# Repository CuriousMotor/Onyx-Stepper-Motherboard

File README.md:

# Onyx-Stepper-Motherboard

The Arduino UNO + CNC shield has been the go-to setup for several CNC machines, robotic arms, drawing machines and what not! It's about time we replace the 8-bit microcontroller, with a powerful 32-bit, Wifi + BLE enabled ESP32!

**Bonus: It's 100% open source, including the PCB layout files!**

This project builds upon pioneering work done by GitHub user [Barton Dring](https://github.com/bdring).

## 3D Model
A 3D model of the PCB can be conveniently viewed in the browser via **CADFlux**.
 - [Basic Model](https://www.cadflux.com/viewer?modelFile=experimental/users/siddharth_kothari/Onyx_PCB_Light.step) (loads faster)
 - [Detailed Model](https://www.cadflux.com/viewer?modelFile=experimental/users/siddharth_kothari/Onyx_PCB.step)

## Blog
[Here's a short blog on how this board was designed!](https://curiousmotor.com/2021/12/27/designing-the-onyx-v1-0-motherboard/)

## Features

1. Control upto 4 stepper motors
2. Supports all stepper drivers in STEP/DIR mode (A4988, DRV8825, TMC2208, TMC2209, TMC2130)
3. 5V PWM outputs x 3
4. Limit switch ports x 3 (X, Y and Z Axes)
5. 12/24V input power supply port
6. Wifi + BLE support (Thanks to GRBL_ESP32)
7. MicroSD card Support

## Firmware

Currently the firmware works superb with GRBL_ESP32. We are in the process of adding support for Marlin.

## Hardware

All of the hardware is designed in **KiCAD**. It's a 2 layer PCB the uses all standard components available at JLCPCB. Currently the board only supports stepper drives in STEP/DIR mode, v2 would support SPI and UART as well.

## Contributors

## Current Progress
Onyx V1 has been thoroughly tested with a 'Dremel CNC', and it works like a charm. We are already ideating and working on a much more powerful V2!

## Support and Sponsorship
We believe open source is the future, collaboration over competition. A lot of time and money goes into development and prototyping. If such projects make your work easier, consider '⭐-ing' the repository. (Yes, that's all it takes!)

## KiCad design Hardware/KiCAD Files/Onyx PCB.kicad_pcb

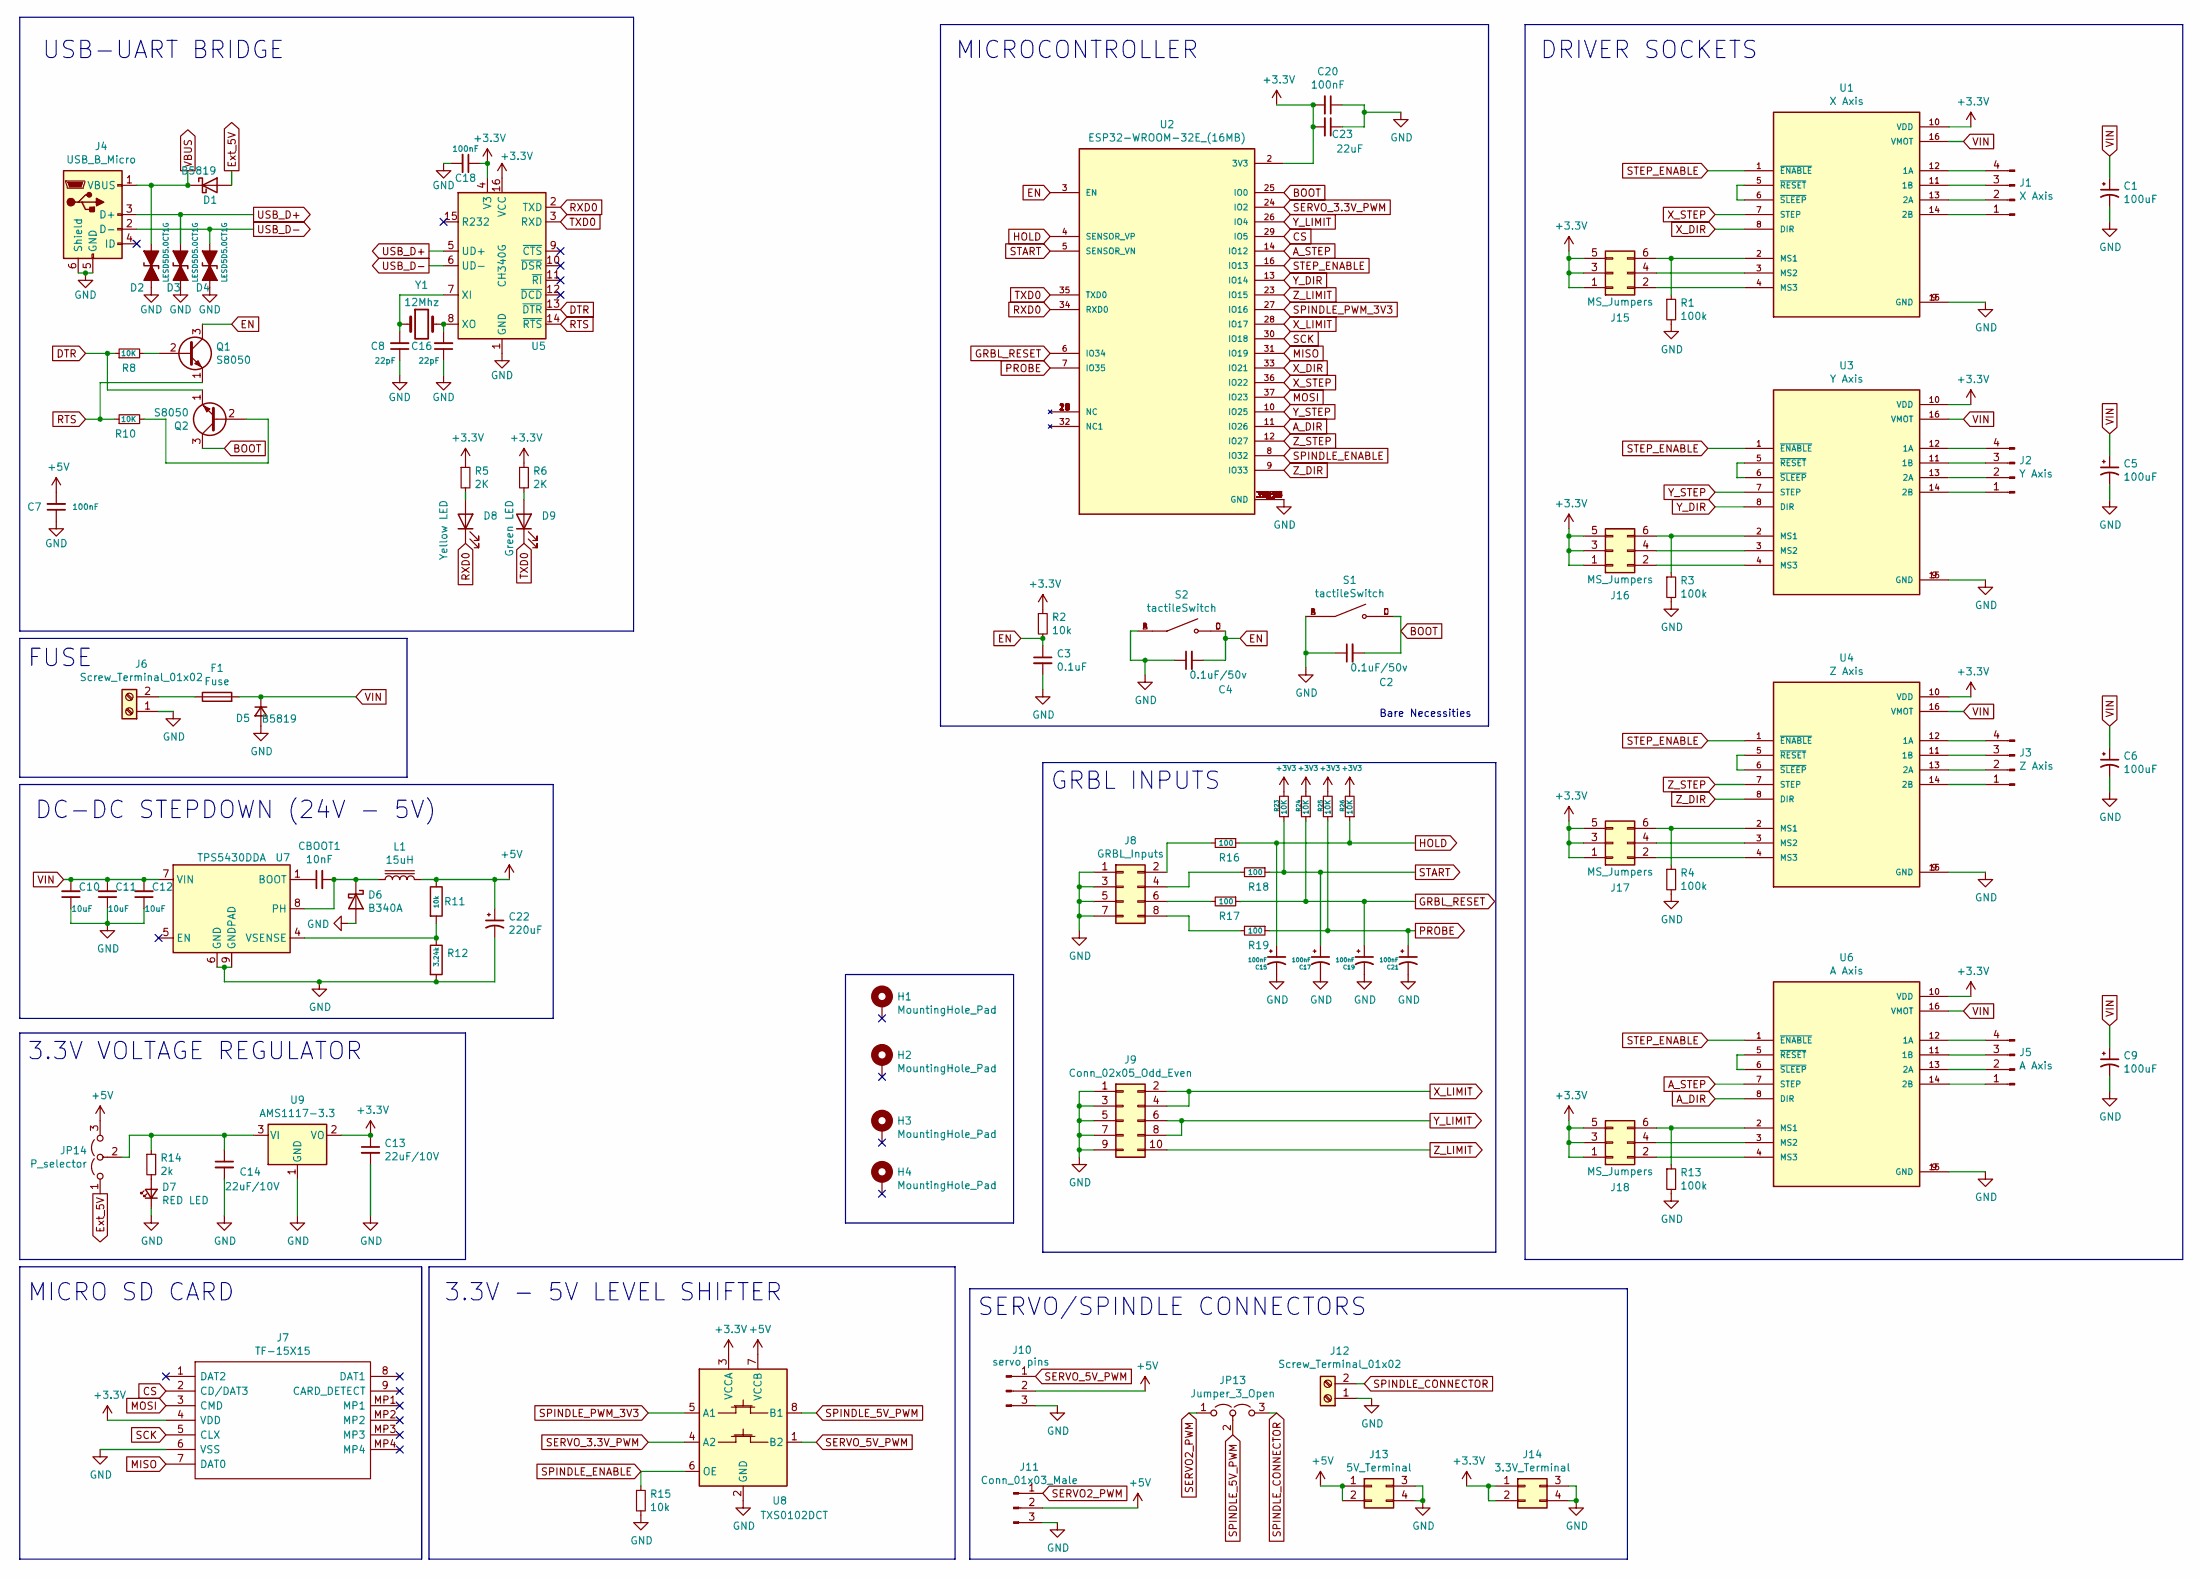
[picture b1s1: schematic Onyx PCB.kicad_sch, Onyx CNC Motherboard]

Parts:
C1, C5, C6, C9: 100uF; CP_Elec_6.3x7.7
C2, C4: 0.1uF/50v; C_0603_1608Metric
C3: 0.1uF; C_0603_1608Metric
C7, C18, C20: 100nF; C_0603_1608Metric
C8, C16: 22pF; C_0603_1608Metric
C10, C11, C12: 10uF; C_0805_2012Metric
C13, C14: 22uF/10V; C_1206_3216Metric
C15, C17, C19, C21: 100nF; C_0402_1005Metric
C22: 220uF; CP_Elec_8x10
C23: 22uF; C_0603_1608Metric; JLCPCB C59461
CBOOT1: 10nF; C_0603_1608Metric
D1, D5: B5819; D_SOD-123
D2, D3, D4: LESD5D5.0CT1G; D_SOD-523
D6: B340A; D_SMA
D7: RED LED; LED_0603_1608Metric
D8: Yellow LED; LED_0603_1608Metric
D9: Green LED; LED_0603_1608Metric
F1: Fuse; R_Axial_DIN0414_L11.9mm_D4.5mm_P20.32mm_Horizontal
H1, H2, H3, H4: MountingHole_Pad; MountingHole_3.2mm_M3_DIN965_Pad
J1: X Axis; PinHeader_1x04_P2.54mm_Vertical
J2: Y Axis; PinHeader_1x04_P2.54mm_Vertical
J3: Z Axis; PinHeader_1x04_P2.54mm_Vertical
J4: USB_B_Micro; USB_Micro-B_Amphenol_10118194_Horizontal; JLCPCB C132563
J5: A Axis; PinHeader_1x04_P2.54mm_Vertical
J6, J12: Screw_Terminal_01x02; TerminalBlock_bornier-2_P5.08mm
J7: TF-15X15; TF15X15; Manufacturer_Part_Number TF-15X15
J8: GRBL_Inputs; PinHeader_2x04_P2.54mm_Vertical
J9: Conn_02x05_Odd_Even; PinHeader_2x05_P2.54mm_Vertical
J10: servo pins; PinHeader_1x03_P2.54mm_Vertical
J11: Conn_01x03_Male; PinHeader_1x03_P2.54mm_Vertical
J13: 5V_Terminal; PinHeader_2x02_P2.54mm_Vertical
J14: 3.3V_Terminal; PinHeader_2x02_P2.54mm_Vertical
J15, J16, J17, J18: MS_Jumpers; PinHeader_2x03_P2.54mm_Vertical
JP13: Jumper_3_Open; PinHeader_1x03_P2.54mm_Vertical
JP14: P_selector; PinHeader_1x03_P2.54mm_Vertical
L1: 15uH; SWRH1207B; JLCPCB C115137
Q1, Q2: S8050; SOT-23
R1: 100k; R_0603_1608Metric; JLCPCB C25803
R2, R11: 10k; R_0805_2012Metric
R3, R4, R13: 100k; R_0603_1608Metric
R5, R6: 2K; R_0805_2012Metric
R8, R10: 10K; R_0805_2012Metric
R12: 3.24k; R_0805_2012Metric
R14: 2k; R_0805_2012Metric
R15: 10k; R_0603_1608Metric
R16, R17, R18, R19: 100; R_0805_2012Metric
R23, R24, R25, R26: 10K; R_0603_1608Metric
S1, S2: tactileSwitch; SW_TS-1187A-B-A-B; PARTREV A0
U1: X Axis; MODULE_A4988_STEPPER_MOTOR_DRIVER_CARRIER
U2: ESP32-WROOM-32E_(16MB); MODULE_ESP32-WROOM-32E_(16MB); PARTREV 1.1
U3: Y Axis; MODULE_A4988_STEPPER_MOTOR_DRIVER_CARRIER
U4: Z Axis; MODULE_A4988_STEPPER_MOTOR_DRIVER_CARRIER
U5: CH340G; SOIC-16_3.9x9.9mm_P1.27mm
U6: A Axis; MODULE_A4988_STEPPER_MOTOR_DRIVER_CARRIER
U7: TPS5430DDA; TI_SO-PowerPAD-8_ThermalVias
U8: TXS0102DCT; SSOP-8_2.95x2.8mm_P0.65mm
U9: AMS1117-3.3; SOT-223-3_TabPin2
Y1: 12Mhz; Crystal_SMD_HC49-SD; JLCPCB C188206

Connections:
+5V: C7.2, C22.1, J10.2, J11.2, J13.1, J13.2, JP14.3 (B), L1.2, R11.1, U8.7 (VCCB)
A_DIR: U2.11 (IO26), U6.8 (DIR)
A_STEP: U2.14 (IO12), U6.7 (STEP)
BOOT: C2.2, Q2.3 (C), S1.C, S1.D, U2.25 (IO0)
CS: J7.2 (CD/DAT3), U2.29 (IO5)
DTR: Q2.1 (E), R8.1, U5.13 (~DTR)
EN: C3.1, C4.2, Q1.3 (C), R2.2, S2.C, S2.D, U2.3 (EN)
Ext_5V: D1.2 (A), JP14.1 (A)
GND: C1.2, C2.1, C3.2, C4.1, C5.2, C6.2, C7.1, C8.1, C9.2, C10.1, C11.1, C12.1, C13.2, C14.2, C15.2, C16.1, C17.2, C18.2, C19.2, C20.1, C21.2, C22.2, C23.1, D2.2 (A2), D3.2 (A2), D4.2 (A2), D5.2 (A), D6.2 (A), D7.1 (K), J4.5 (GND), J4.6 (Shield), J6.1, J7.6 (VSS), J8.1, J8.3, J8.5, J8.7, J9.1, J9.3, J9.5, J9.7, J9.9, J10.3, J11.3, J12.1, J13.3, J13.4, J14.3, J14.4, R1.2, R3.2, R4.2, R12.2, R13.2, R15.2, S1.A, S1.B, S2.A, S2.B, U1.9 (GND), U1.15 (GND), U2.1 (GND), U2.15 (GND), U2.38 (GND), U2.39_1 (GND), U2.39_2 (GND), U2.39_3 (GND), U2.39_4 (GND), U2.39_5 (GND), U2.39_6 (GND), U2.39_7 (GND), U2.39_8 (GND), U2.39_9 (GND), U2.39_10 (GND), U2.39_11 (GND), U2.39_12 (GND), U2.39_13 (GND), U2.39_14 (GND), U2.39_15 (GND), U2.39_16 (GND), U2.39_17 (GND), U2.39_18 (GND), U2.39_19 (GND), U2.39_20 (GND), U2.39_21 (GND), U3.9 (GND), U3.15 (GND), U4.9 (GND), U4.15 (GND), U5.1 (GND), U6.9 (GND), U6.15 (GND), U7.6 (GND), U7.9 (GNDPAD), U8.2 (GND), U9.1 (GND)
GRBL_RESET: C19.1, R17.1, R24.1, U2.6 (IO34)
HOLD: C15.1, R16.1, R26.1, U2.4 (SENSOR_VP)
MISO: J7.7 (DAT0), U2.31 (IO19)
MOSI: J7.3 (CMD), U2.37 (IO23)
unnamed: C8.2, U5.7 (XI), Y1.1
unnamed: C14.1, JP14.2 (C), R14.1, U9.3 (VI)
unnamed: C16.2, U5.8 (XO), Y1.2
unnamed: CBOOT1.1, U7.1 (BOOT)
unnamed: CBOOT1.2, D6.1 (K), L1.1, U7.8 (PH)
unnamed: D7.2 (A), R14.2
unnamed: D8.2 (A), R5.2
unnamed: D9.2 (A), R6.2
unnamed: F1.1, J6.2
unnamed: J1.1, U1.14 (2B)
unnamed: J1.2, U1.13 (2A)
unnamed: J1.3, U1.11 (1B)
unnamed: J1.4, U1.12 (1A)
unnamed: J2.1, U3.14 (2B)
unnamed: J2.2, U3.13 (2A)
unnamed: J2.3, U3.11 (1B)
unnamed: J2.4, U3.12 (1A)
unnamed: J3.1, U4.14 (2B)
unnamed: J3.2, U4.13 (2A)
unnamed: J3.3, U4.11 (1B)
unnamed: J3.4, U4.12 (1A)
unnamed: J5.1, U6.14 (2B)
unnamed: J5.2, U6.13 (2A)
unnamed: J5.3, U6.11 (1B)
unnamed: J5.4, U6.12 (1A)
unnamed: J8.2, R16.2
unnamed: J8.4, R18.2
unnamed: J8.6, R17.2
unnamed: J8.8, R19.2
unnamed: J15.2, U1.4 (MS3)
unnamed: J15.4, U1.3 (MS2)
unnamed: J15.6, R1.1, U1.2 (MS1)
unnamed: J16.2, U3.4 (MS3)
unnamed: J16.4, U3.3 (MS2)
unnamed: J16.6, R3.1, U3.2 (MS1)
unnamed: J17.2, U4.4 (MS3)
unnamed: J17.4, U4.3 (MS2)
unnamed: J17.6, R4.1, U4.2 (MS1)
unnamed: J18.2, U6.4 (MS3)
unnamed: J18.4, U6.3 (MS2)
unnamed: J18.6, R13.1, U6.2 (MS1)
unnamed: Q1.2 (B), R8.2
unnamed: Q2.2 (B), R10.2
unnamed: R11.2, R12.1, U7.4 (VSENSE)
unnamed: U1.5 (~RESET), U1.6 (~SLEEP)
unnamed: U3.5 (~RESET), U3.6 (~SLEEP)
unnamed: U4.5 (~RESET), U4.6 (~SLEEP)
unnamed: U6.5 (~RESET), U6.6 (~SLEEP)
PROBE: C21.1, R19.1, R25.1, U2.7 (IO35)
RTS: Q1.1 (E), R10.1, U5.14 (~RTS)
RXD0: D8.1 (K), U2.34 (RXD0), U5.2 (TXD)
SCK: J7.5 (CLX), U2.30 (IO18)
SERVO2_PWM: J11.1, JP13.1 (A)
SERVO_3.3V_PWM: U2.24 (IO2), U8.4 (A2)
SERVO_5V_PWM: J10.1, U8.1 (B2)
SPINDLE_5V_PWM: JP13.2 (C), U8.8 (B1)
SPINDLE_CONNECTOR: J12.2, JP13.3 (B)
SPINDLE_ENABLE: R15.1, U2.8 (IO32), U8.6 (OE)
SPINDLE_PWM_3V3: U2.27 (IO16), U8.5 (A1)
START: C17.1, R18.1, R23.1, U2.5 (SENSOR_VN)
STEP_ENABLE: U1.1 (~ENABLE), U2.16 (IO13), U3.1 (~ENABLE), U4.1 (~ENABLE), U6.1 (~ENABLE)
TXD0: D9.1 (K), U2.35 (TXD0), U5.3 (RXD)
USB_D+: D3.1 (A1), J4.3 (D+), U5.5 (UD+)
USB_D-: D4.1 (A1), J4.2 (D-), U5.6 (UD-)
VBUS: D1.1 (K), D2.1 (A1), J4.1 (VBUS)
VIN: C1.1, C5.1, C6.1, C9.1, C10.2, C11.2, C12.2, D5.1 (K), F1.2, U1.16 (VMOT), U3.16 (VMOT), U4.16 (VMOT), U6.16 (VMOT), U7.7 (VIN)
X_DIR: U1.8 (DIR), U2.33 (IO21)
X_LIMIT: J9.2, J9.4, U2.28 (IO17)
X_STEP: U1.7 (STEP), U2.36 (IO22)
Y_DIR: U2.13 (IO14), U3.8 (DIR)
Y_LIMIT: J9.6, J9.8, U2.26 (IO4)
Y_STEP: U2.10 (IO25), U3.7 (STEP)
Z_DIR: U2.9 (IO33), U4.8 (DIR)
Z_LIMIT: J9.10, U2.23 (IO15)
Z_STEP: U2.12 (IO27), U4.7 (STEP)

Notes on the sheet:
DRIVER SOCKETS
Bare Necessities
3.3V VOLTAGE REGULATOR
FUSE
SERVO/SPINDLE CONNECTORS
3.3V - 5V LEVEL SHIFTER
MICRO SD CARD
MICROCONTROLLER
DC-DC STEPDOWN (24V - 5V)
USB-UART BRIDGE
GRBL INPUTS

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
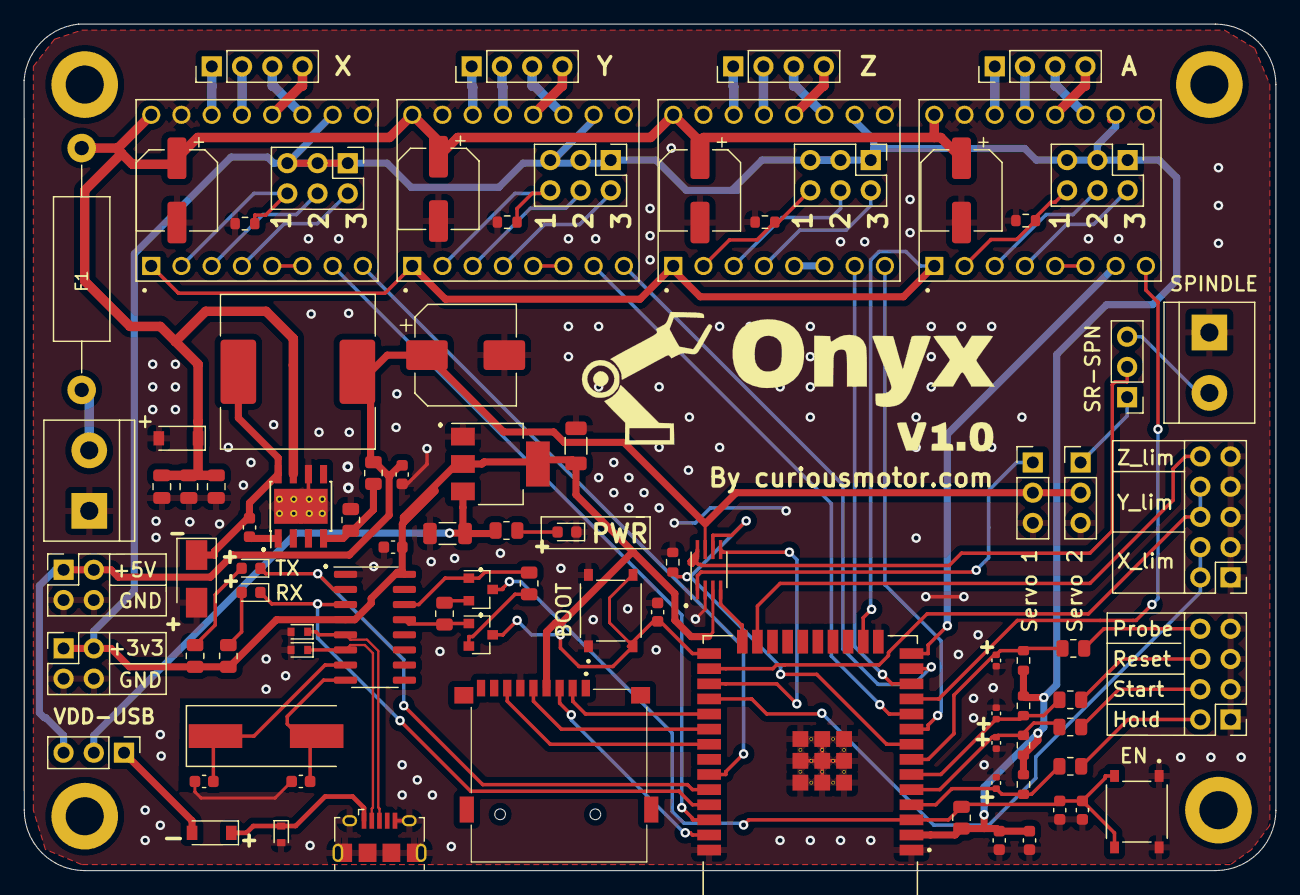
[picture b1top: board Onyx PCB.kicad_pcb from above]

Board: 2 copper layers, 105.2 x 71.1 mm, 94 parts (0 on the bottom side), 89 nets.

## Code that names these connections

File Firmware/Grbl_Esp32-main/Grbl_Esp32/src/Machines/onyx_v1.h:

#pragma once
// clang-format off

/*
    onyx_v1.0.h
    Part of Grbl_ESP32

    Pin assignments for onyx v1.0 stepper motherboard

    2019    - Bart Dring
    2020    - Mitch Bradley

    Grbl_ESP32 is free software: you can redistribute it and/or modify
    it under the terms of the GNU General Public License as published by
    the Free Software Foundation, either version 3 of the License, or
    (at your option) any later version.

    Grbl is distributed in the hope that it will be useful,
    but WITHOUT ANY WARRANTY; without even the implied warranty of
    MERCHANTABILITY or FITNESS FOR A PARTICULAR PURPOSE.  See the
    GNU General Public License for more details.

    You should have received a copy of the GNU General Public License
    along with Grbl_ESP32.  If not, see <http://www.gnu.org/licenses/>.
*/



#define MACHINE_NAME "OnyxV1.0"

#define N_AXIS 4

#define X_STEP_PIN      GPIO_NUM_22
#define X_DIRECTION_PIN GPIO_NUM_21

#define Y_STEP_PIN      GPIO_NUM_25
#define Y_DIRECTION_PIN GPIO_NUM_14

#define Z_STEP_PIN      GPIO_NUM_27
#define Z_DIRECTION_PIN GPIO_NUM_33

#define Y2_STEP_PIN      GPIO_NUM_12
#define Y2_DIRECTION_PIN GPIO_NUM_26



// OK to comment out to use pin for other features
#define STEPPERS_DISABLE_PIN GPIO_NUM_13

// Note: if you use PWM rather than relay, you could map GPIO_NUM_2 to mist or flood
//#define USE_SPINDLE_RELAY

#ifdef USE_SPINDLE_RELAY
    #define SPINDLE_TYPE SpindleType::RELAY
    #define SPINDLE_OUTPUT_PIN GPIO_NUM_17
#else
    #define SPINDLE_TYPE SpindleType::PWM
    #define SPINDLE_OUTPUT_PIN GPIO_NUM_2

    #define SPINDLE_ENABLE_PIN GPIO_NUM_32
#endif

// Note: Only uncomment this if USE_SPINDLE_RELAY is commented out.
// Relay can be used for spindle or either coolant
//#define COOLANT_FLOOD_PIN     GPIO_NUM_2
//#define COOLANT_MIST_PIN      GPIO_NUM_2


#define X_LIMIT_PIN             GPIO_NUM_17
#define Y_LIMIT_PIN             GPIO_NUM_4
#define Z_LIMIT_PIN             GPIO_NUM_15

#define PROBE_PIN               GPIO_NUM_35

// The default value in config.h is wrong for this controller
#ifdef INVERT_CONTROL_PIN_MASK
    #undef INVERT_CONTROL_PIN_MASK
#endif

#define INVERT_CONTROL_PIN_MASK B1110

#define CONTROL_RESET_PIN           GPIO_NUM_34  // needs external pullup
#define CONTROL_FEED_HOLD_PIN       GPIO_NUM_36  // needs external pullup
#define CONTROL_CYCLE_START_PIN     GPIO_NUM_39  // needs external pullup

#define DEFAULT_STEP_PULSE_MICROSECONDS     3
#define DEFAULT_STEPPER_IDLE_LOCK_TIME      255 //  255 = Keep steppers on

#define DEFAULT_STEPPING_INVERT_MASK    0 // uint8_t
#define DEFAULT_DIRECTION_INVERT_MASK   0 // uint8_t
#define DEFAULT_INVERT_ST_ENABLE        0 // boolean
#define DEFAULT_INVERT_LIMIT_PINS       1 // boolean
#define DEFAULT_INVERT_PROBE_PIN        0 // boolean

#define DEFAULT_STATUS_REPORT_MASK 1

#define DEFAULT_JUNCTION_DEVIATION  0.01 // mm
#define DEFAULT_ARC_TOLERANCE       0.002 // mm
#define DEFAULT_REPORT_INCHES       0 // false

#define DEFAULT_SOFT_LIMIT_ENABLE 0 // false
#define DEFAULT_HARD_LIMIT_ENABLE 0  // false

#define DEFAULT_HOMING_ENABLE           1  // false
#define DEFAULT_HOMING_DIR_MASK         3 // move positive dir Z,negative X,Y
#define DEFAULT_HOMING_FEED_RATE        100.0 // mm/min
#define DEFAULT_HOMING_SEEK_RATE        200.0 // mm/min
#define DEFAULT_HOMING_DEBOUNCE_DELAY   250 // msec (0-65k)
#define DEFAULT_HOMING_PULLOFF          2.0 // mm

#ifdef USE_SPINDLE_RELAY
    #define DEFAULT_SPINDLE_RPM_MAX 1.0 // must be 1 so PWM duty is alway 100% to prevent relay damage
#else
    #define DEFAULT_SPINDLE_RPM_MAX 1000.0 // can be change to your spindle max
#endif

#define DEFAULT_SPINDLE_RPM_MIN 0.0 // rpm

#define DEFAULT_LASER_MODE 0 // false

#define DEFAULT_X_STEPS_PER_MM 800.0
#define DEFAULT_Y_STEPS_PER_MM 800.0
#define DEFAULT_Z_STEPS_PER_MM 800.0

#define DEFAULT_X_MAX_RATE 8000.0 // mm/min
#define DEFAULT_Y_MAX_RATE 8000.0 // mm/min
#define DEFAULT_Z_MAX_RATE 3000.0 // mm/min

#define DEFAULT_X_ACCELERATION 200.0 // mm/sec^2
#define DEFAULT_Y_ACCELERATION 200.0 // mm/sec^2
#define DEFAULT_Z_ACCELERATION 100.0 // mm/sec^2

#define DEFAULT_X_MAX_TRAVEL 500.0 // mm NOTE: Must be a positive value.
#define DEFAULT_Y_MAX_TRAVEL 500.0 // mm NOTE: Must be a positive value.
#define DEFAULT_Z_MAX_TRAVEL 80.0 // mm NOTE: Must be a positive value.

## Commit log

2021-12-15 Added readMe
2021-12-15 More detail in ReadMe
2021-12-15 Resized images in readme
2021-12-15 Edits in readme
2021-12-19 Further elaborated readme
2021-12-19 Further Readme changes
2021-12-19 Added Hardware files
2021-12-19 Fixed picture alignment
2021-12-19 Changes in ReadMe
2021-12-19 Changes to ReadMe
2021-12-19 Added more GND Vias
2021-12-21 Re-created step file with corrected drivers
2021-12-22 Fixed bug from V1.0
2021-12-28 Added 3D model
2021-12-28 Revised ReadMe
2021-12-28 Added links to CADFlux models
2021-12-30 Changed individual MS-config jumpers to blocks for easier soldering
2022-01-01 Updated 3D model
